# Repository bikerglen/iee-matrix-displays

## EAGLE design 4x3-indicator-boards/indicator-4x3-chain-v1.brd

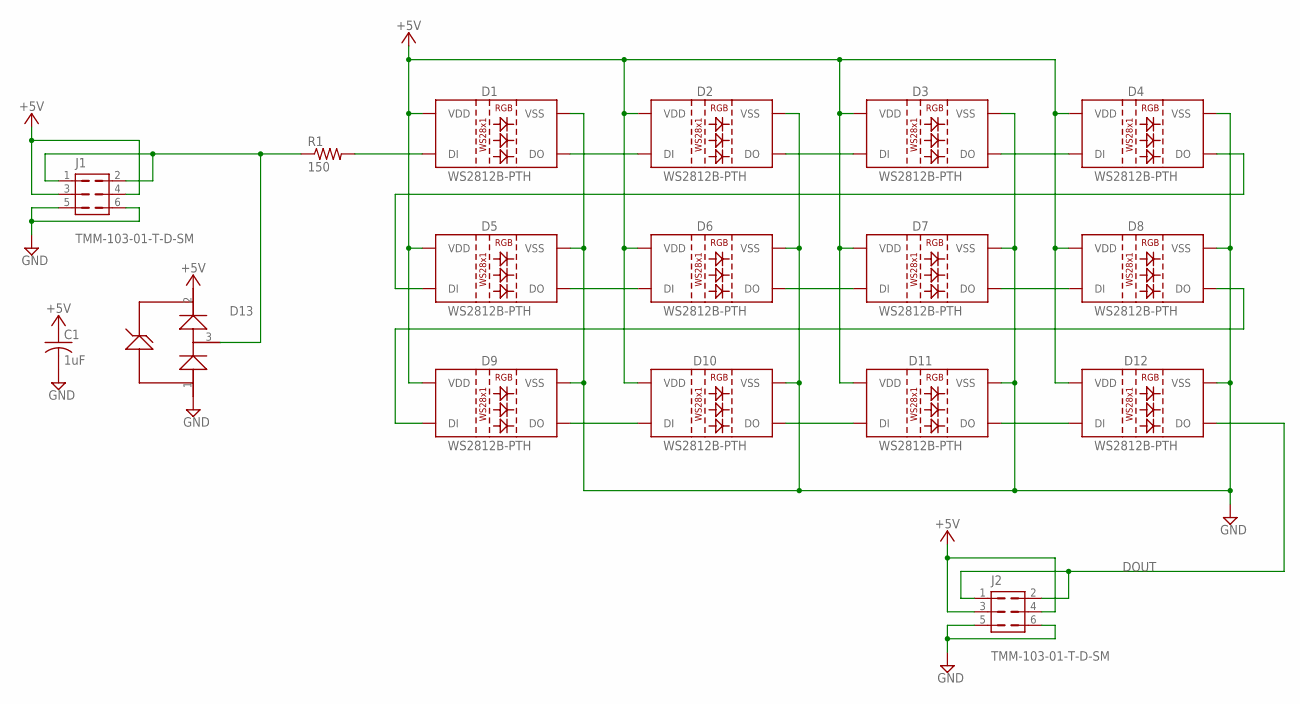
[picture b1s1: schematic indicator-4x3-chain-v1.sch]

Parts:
C1: 1uF; C0603K
D1, D2, D3, D4, D5, D6, D7, D8, D9, D10, D11, D12: WS2812B-PTH; WS2812B-PTH-KIT
D13: DRTR5V0U1SO; SOT23-3; MFR_PART_NO DRTR5V0U1SO
J1, J2: TMM-103-01-T-D-SM; 2MM-SMD-HEADER-2X3
R1: 150; R0603

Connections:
+5V: C1.1, D1.2 (VDD), D2.2 (VDD), D3.2 (VDD), D4.2 (VDD), D5.2 (VDD), D6.2 (VDD), D7.2 (VDD), D8.2 (VDD), D9.2 (VDD), D10.2 (VDD), D11.2 (VDD), D12.2 (VDD), D13.2, J1.3, J1.4, J2.3, J2.4
DIN: D13.3 (1), J1.1, J1.2, R1.1
DOUT: D12.4 (DO), J2.1, J2.2
GND: C1.2, D1.3 (VSS), D2.3 (VSS), D3.3 (VSS), D4.3 (VSS), D5.3 (VSS), D6.3 (VSS), D7.3 (VSS), D8.3 (VSS), D9.3 (VSS), D10.3 (VSS), D11.3 (VSS), D12.3 (VSS), D13.1 (3), J1.5, J1.6, J2.5, J2.6
unnamed: D5.4 (DO), D6.1 (DI)
unnamed: D6.4 (DO), D7.1 (DI)
unnamed: D1.4 (DO), D2.1 (DI)
unnamed: D2.4 (DO), D3.1 (DI)
unnamed: D3.4 (DO), D4.1 (DI)
unnamed: D7.4 (DO), D8.1 (DI)
unnamed: D4.4 (DO), D5.1 (DI)
unnamed: D9.4 (DO), D10.1 (DI)
unnamed: D10.4 (DO), D11.1 (DI)
unnamed: D11.4 (DO), D12.1 (DI)
unnamed: D1.1 (DI), R1.2
unnamed: D8.4 (DO), D9.1 (DI)

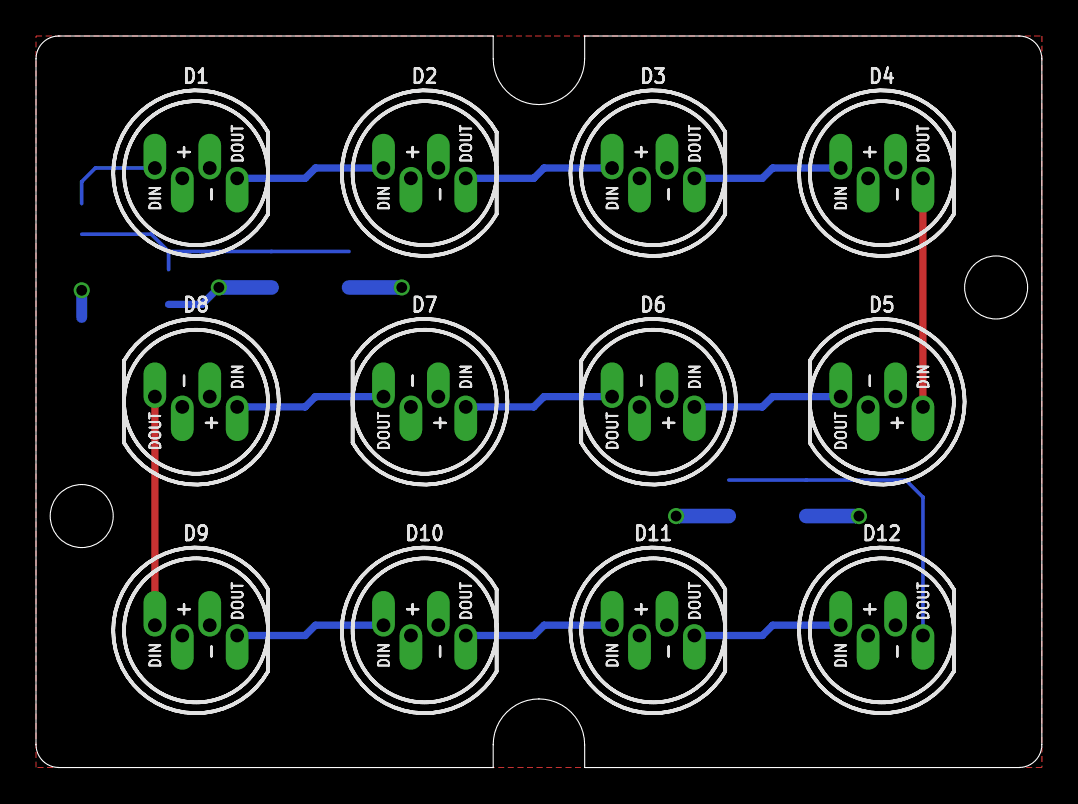
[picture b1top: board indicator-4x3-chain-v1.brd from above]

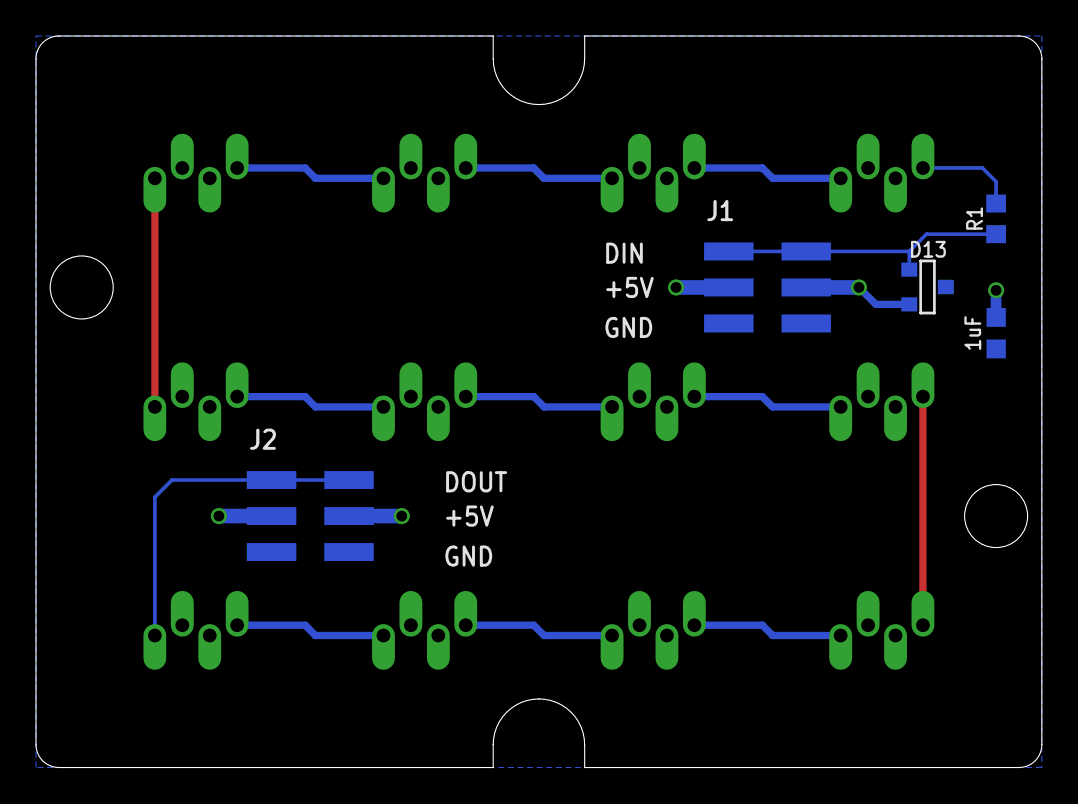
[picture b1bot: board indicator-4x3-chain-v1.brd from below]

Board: 2 copper layers, 55.9 x 40.6 mm, 17 parts (5 on the bottom side), 16 nets.

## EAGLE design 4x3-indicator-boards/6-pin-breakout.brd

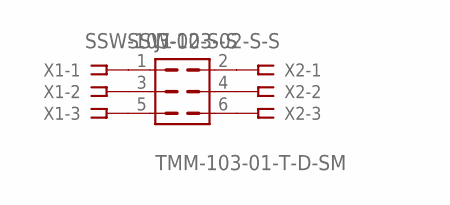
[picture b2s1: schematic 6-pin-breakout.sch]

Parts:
J1: TMM-103-01-T-D-SM; 2MM-SMD-HEADER-2X3
X1, X2: SSW-103-02-S-S

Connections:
unnamed: J1.1, X1.1
unnamed: J1.3, X1.2
unnamed: J1.5, X1.3
unnamed: J1.2, X2.1
unnamed: J1.4, X2.2
unnamed: J1.6, X2.3

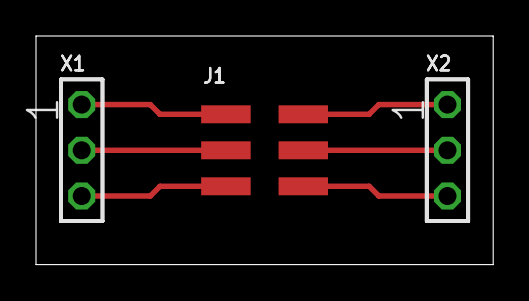
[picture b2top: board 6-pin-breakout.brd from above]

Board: 2 copper layers, 25.4 x 12.7 mm, 3 parts (0 on the bottom side), 6 nets.

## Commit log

2022-11-28 initial checkin

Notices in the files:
parts and their libraries:
SparkFun-LED: Licensing: Creative Commons ShareAlike 4.0 International - https://creativecommons.org/licenses/by-sa/4.0
